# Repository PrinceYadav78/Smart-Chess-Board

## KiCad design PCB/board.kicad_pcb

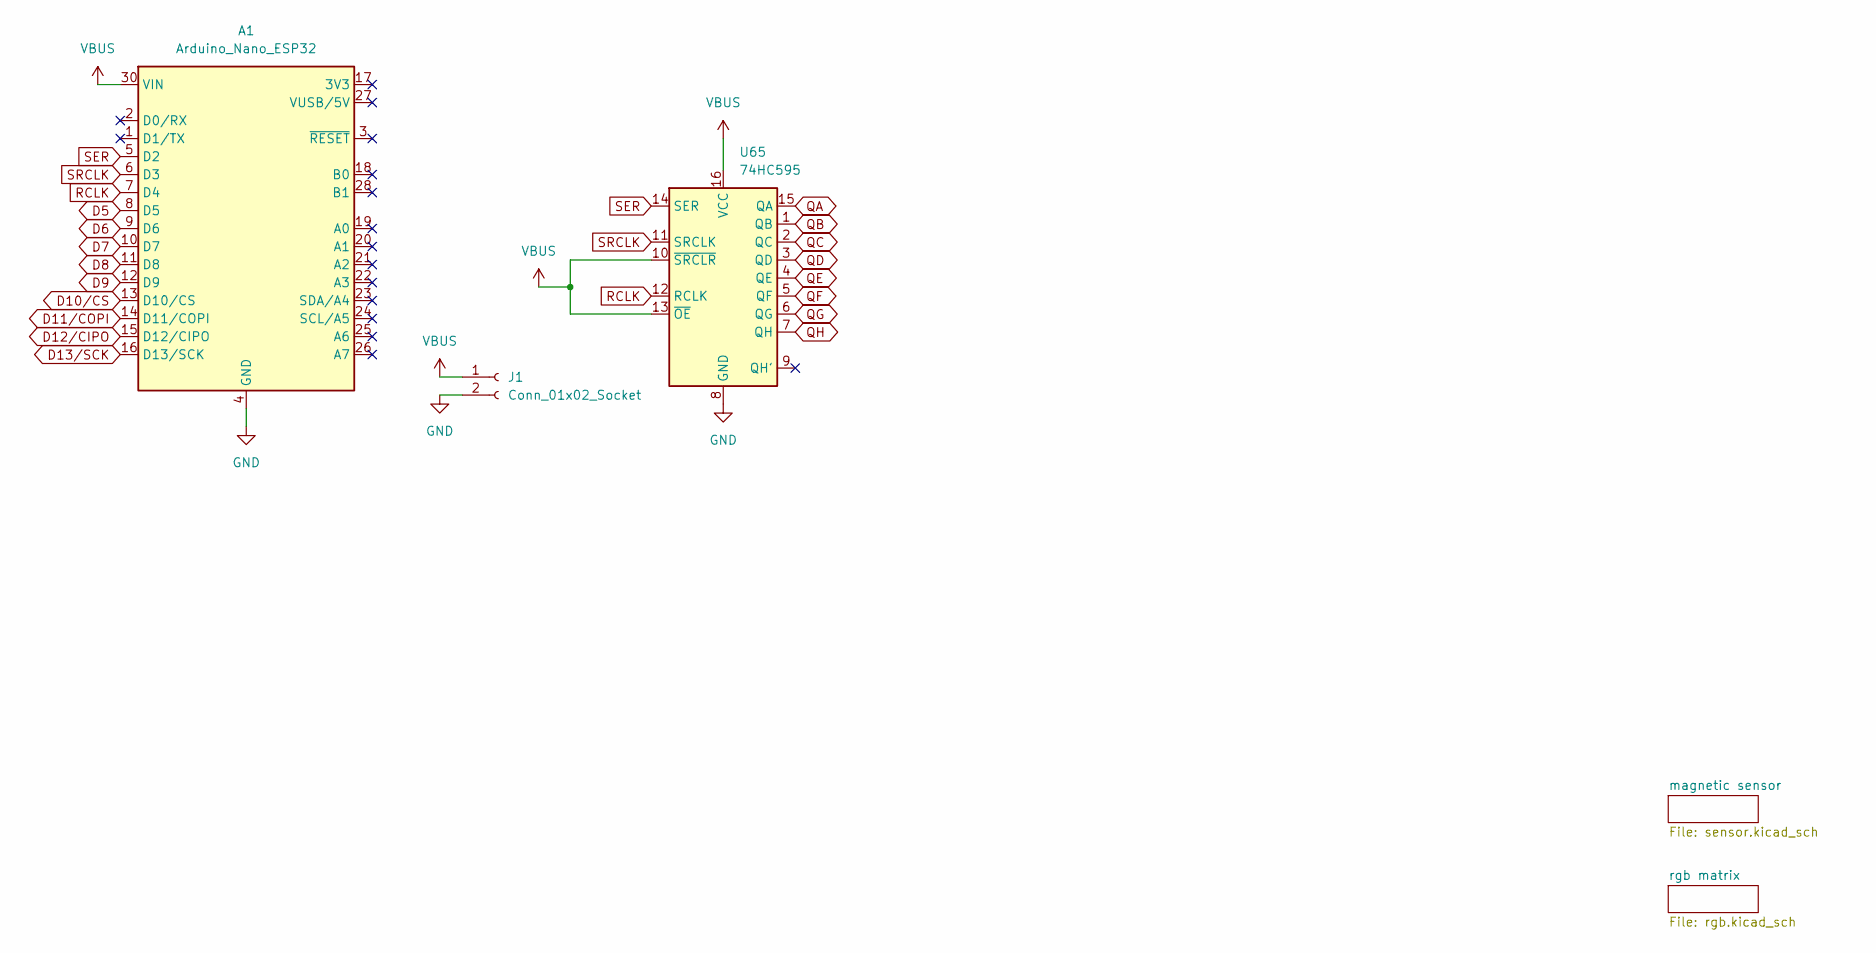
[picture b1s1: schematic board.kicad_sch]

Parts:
A1: Arduino_Nano_ESP32; Arduino_Nano
J1: Conn_01x02_Socket; Hirose_DF63R-2P-3.96DSA_1x02_P3.96mm_Vertical
U65: 74HC595; DIP-16_W7.62mm

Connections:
D5: A1.8 (D5); also elsewhere on the board
D6: A1.9 (D6); also elsewhere on the board
D7: A1.10 (D7); also elsewhere on the board
D8: A1.11 (D8); also elsewhere on the board
D9: A1.12 (D9); also elsewhere on the board
D10/CS: A1.13 (D10/CS); also elsewhere on the board
D11/COPI: A1.14 (D11/COPI); also elsewhere on the board
D12/CIPO: A1.15 (D12/CIPO); also elsewhere on the board
D13/SCK: A1.16 (D13/SCK); also elsewhere on the board
GND: A1.4 (GND), A1.29 (GND), J1.2, U65.8 (GND); also elsewhere on the board
QA: U65.15 (QA); also elsewhere on the board
QB: U65.1 (QB); also elsewhere on the board
QC: U65.2 (QC); also elsewhere on the board
QD: U65.3 (QD); also elsewhere on the board
QE: U65.4 (QE); also elsewhere on the board
QF: U65.5 (QF); also elsewhere on the board
QG: U65.6 (QG); also elsewhere on the board
QH: U65.7 (QH); also elsewhere on the board
RCLK: A1.7 (D4), U65.12 (RCLK)
SER: A1.5 (D2), U65.14 (SER)
SRCLK: A1.6 (D3), U65.11 (SRCLK)
VBUS: A1.30 (VIN), J1.1, U65.10 (~SRCLR), U65.13 (~OE), U65.16 (VCC); also elsewhere on the board

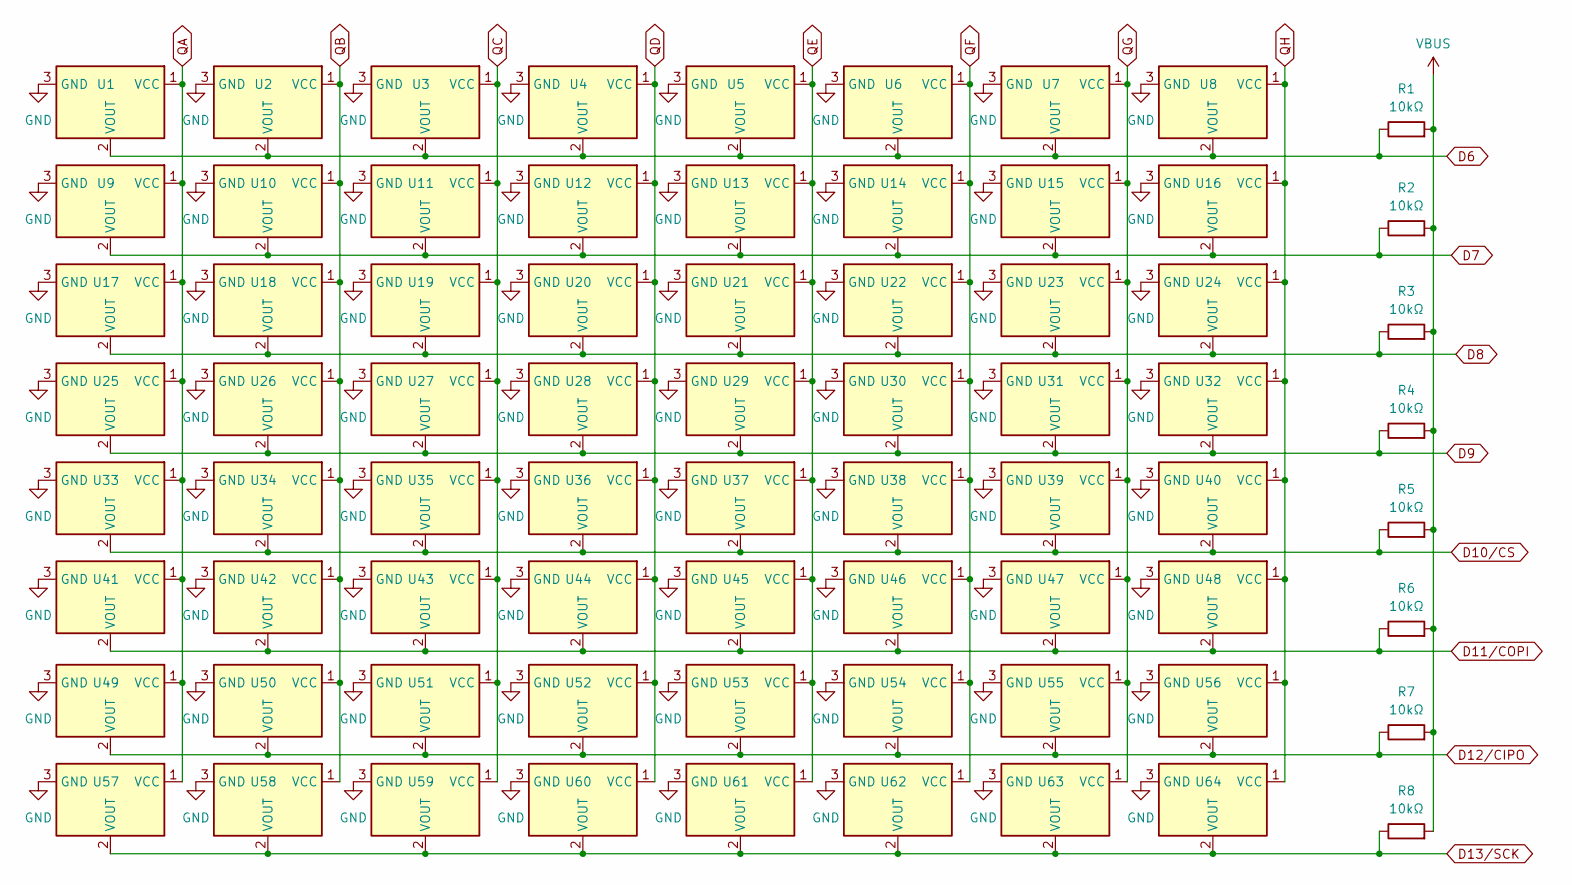
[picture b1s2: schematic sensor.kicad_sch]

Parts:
R1, R2, R3, R4, R5, R6, R7, R8: 10kΩ; R_0805_2012Metric
U1, U2, U3, U4, U5, U6, U7, U8, U9, U10, U11, U12, U13, U14, U15, U16, U17, U18, U19, U20, U21, U22, U23, U24, U25, U26, U27, U28, U29, U30, U31, U32, U33, U34, U35, U36, U37, U38, U39, U40, U41, U42, U43, U44, U45, U46, U47, U48, U49, U50, U51, U52, U53, U54, U55, U56, U57, U58, U59, U60, U61, U62, U63, U64: A3144E; SOT-23

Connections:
D6: R1.1, U1.2 (VOUT), U2.2 (VOUT), U3.2 (VOUT), U4.2 (VOUT), U5.2 (VOUT), U6.2 (VOUT), U7.2 (VOUT), U8.2 (VOUT); also elsewhere on the board
D7: R2.1, U9.2 (VOUT), U10.2 (VOUT), U11.2 (VOUT), U12.2 (VOUT), U13.2 (VOUT), U14.2 (VOUT), U15.2 (VOUT), U16.2 (VOUT); also elsewhere on the board
D8: R3.1, U17.2 (VOUT), U18.2 (VOUT), U19.2 (VOUT), U20.2 (VOUT), U21.2 (VOUT), U22.2 (VOUT), U23.2 (VOUT), U24.2 (VOUT); also elsewhere on the board
D9: R4.1, U25.2 (VOUT), U26.2 (VOUT), U27.2 (VOUT), U28.2 (VOUT), U29.2 (VOUT), U30.2 (VOUT), U31.2 (VOUT), U32.2 (VOUT); also elsewhere on the board
D10/CS: R5.1, U33.2 (VOUT), U34.2 (VOUT), U35.2 (VOUT), U36.2 (VOUT), U37.2 (VOUT), U38.2 (VOUT), U39.2 (VOUT), U40.2 (VOUT); also elsewhere on the board
D11/COPI: R6.1, U41.2 (VOUT), U42.2 (VOUT), U43.2 (VOUT), U44.2 (VOUT), U45.2 (VOUT), U46.2 (VOUT), U47.2 (VOUT), U48.2 (VOUT); also elsewhere on the board
D12/CIPO: R7.1, U49.2 (VOUT), U50.2 (VOUT), U51.2 (VOUT), U52.2 (VOUT), U53.2 (VOUT), U54.2 (VOUT), U55.2 (VOUT), U56.2 (VOUT); also elsewhere on the board
D13/SCK: R8.1, U57.2 (VOUT), U58.2 (VOUT), U59.2 (VOUT), U60.2 (VOUT), U61.2 (VOUT), U62.2 (VOUT), U63.2 (VOUT), U64.2 (VOUT); also elsewhere on the board
GND: U1.3 (GND), U2.3 (GND), U3.3 (GND), U4.3 (GND), U5.3 (GND), U6.3 (GND), U7.3 (GND), U8.3 (GND), U9.3 (GND), U10.3 (GND), U11.3 (GND), U12.3 (GND), U13.3 (GND), U14.3 (GND), U15.3 (GND), U16.3 (GND), U17.3 (GND), U18.3 (GND), U19.3 (GND), U20.3 (GND), U21.3 (GND), U22.3 (GND), U23.3 (GND), U24.3 (GND), U25.3 (GND), U26.3 (GND), U27.3 (GND), U28.3 (GND), U29.3 (GND), U30.3 (GND), U31.3 (GND), U32.3 (GND), U33.3 (GND), U34.3 (GND), U35.3 (GND), U36.3 (GND), U37.3 (GND), U38.3 (GND), U39.3 (GND), U40.3 (GND), U41.3 (GND), U42.3 (GND), U43.3 (GND), U44.3 (GND), U45.3 (GND), U46.3 (GND), U47.3 (GND), U48.3 (GND), U49.3 (GND), U50.3 (GND), U51.3 (GND), U52.3 (GND), U53.3 (GND), U54.3 (GND), U55.3 (GND), U56.3 (GND), U57.3 (GND), U58.3 (GND), U59.3 (GND), U60.3 (GND), U61.3 (GND), U62.3 (GND), U63.3 (GND), U64.3 (GND); also elsewhere on the board
QA: U1.1 (VCC), U9.1 (VCC), U17.1 (VCC), U25.1 (VCC), U33.1 (VCC), U41.1 (VCC), U49.1 (VCC), U57.1 (VCC); also elsewhere on the board
QB: U2.1 (VCC), U10.1 (VCC), U18.1 (VCC), U26.1 (VCC), U34.1 (VCC), U42.1 (VCC), U50.1 (VCC), U58.1 (VCC); also elsewhere on the board
QC: U3.1 (VCC), U11.1 (VCC), U19.1 (VCC), U27.1 (VCC), U35.1 (VCC), U43.1 (VCC), U51.1 (VCC), U59.1 (VCC); also elsewhere on the board
QD: U4.1 (VCC), U12.1 (VCC), U20.1 (VCC), U28.1 (VCC), U36.1 (VCC), U44.1 (VCC), U52.1 (VCC), U60.1 (VCC); also elsewhere on the board
QE: U5.1 (VCC), U13.1 (VCC), U21.1 (VCC), U29.1 (VCC), U37.1 (VCC), U45.1 (VCC), U53.1 (VCC), U61.1 (VCC); also elsewhere on the board
QF: U6.1 (VCC), U14.1 (VCC), U22.1 (VCC), U30.1 (VCC), U38.1 (VCC), U46.1 (VCC), U54.1 (VCC), U62.1 (VCC); also elsewhere on the board
QG: U7.1 (VCC), U15.1 (VCC), U23.1 (VCC), U31.1 (VCC), U39.1 (VCC), U47.1 (VCC), U55.1 (VCC), U63.1 (VCC); also elsewhere on the board
QH: U8.1 (VCC), U16.1 (VCC), U24.1 (VCC), U32.1 (VCC), U40.1 (VCC), U48.1 (VCC), U56.1 (VCC), U64.1 (VCC); also elsewhere on the board
VBUS: R1.2, R2.2, R3.2, R4.2, R5.2, R6.2, R7.2, R8.2; also elsewhere on the board

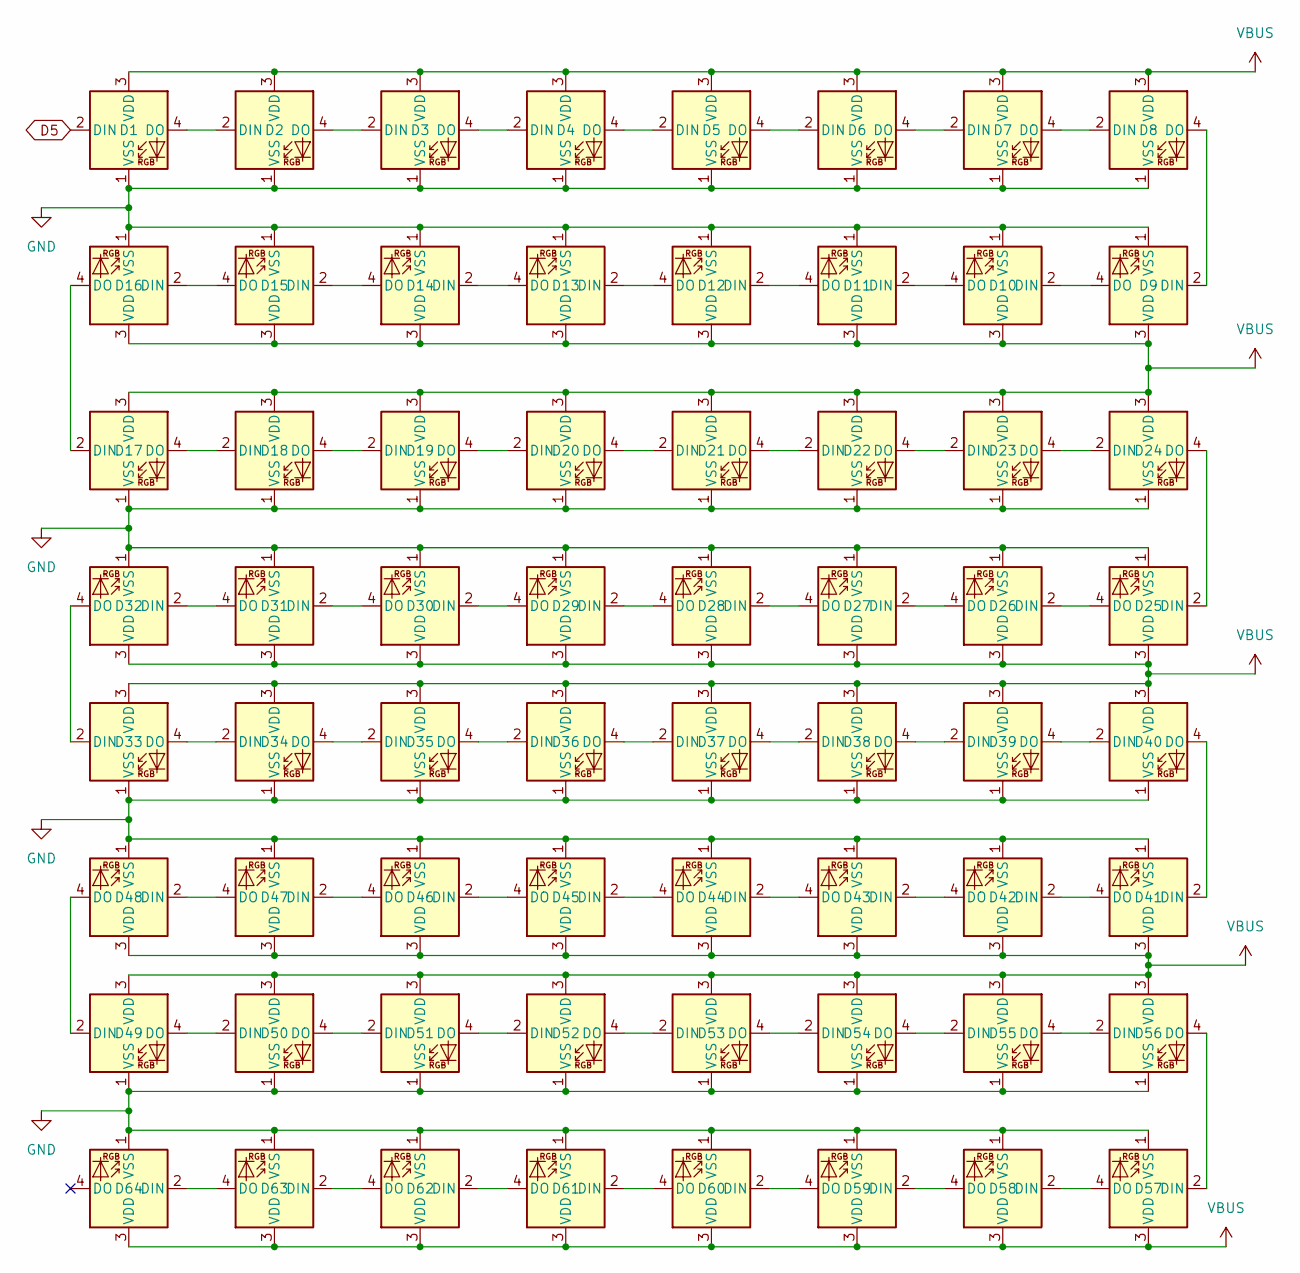
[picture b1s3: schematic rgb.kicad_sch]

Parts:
D1, D2, D3, D4, D5, D6, D7, D8, D9, D10, D11, D12, D13, D14, D15, D16, D17, D18, D19, D20, D21, D22, D23, D24, D25, D26, D27, D28, D29, D30, D31, D32, D33, D34, D35, D36, D37, D38, D39, D40, D41, D42, D43, D44, D45, D46, D47, D48, D49, D50, D51, D52, D53, D54, D55, D56, D57, D58, D59, D60, D61, D62, D63, D64: Inolux_IN-PI554FCH; LED_Inolux_IN-PI554FCH_PLCC4_5.0x5.0mm_P3.2mm

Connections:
D5: D1.2 (DIN); also elsewhere on the board
GND: D1.1 (VSS), D2.1 (VSS), D3.1 (VSS), D4.1 (VSS), D5.1 (VSS), D6.1 (VSS), D7.1 (VSS), D8.1 (VSS), D9.1 (VSS), D10.1 (VSS), D11.1 (VSS), D12.1 (VSS), D13.1 (VSS), D14.1 (VSS), D15.1 (VSS), D16.1 (VSS), D17.1 (VSS), D18.1 (VSS), D19.1 (VSS), D20.1 (VSS), D21.1 (VSS), D22.1 (VSS), D23.1 (VSS), D24.1 (VSS), D25.1 (VSS), D26.1 (VSS), D27.1 (VSS), D28.1 (VSS), D29.1 (VSS), D30.1 (VSS), D31.1 (VSS), D32.1 (VSS), D33.1 (VSS), D34.1 (VSS), D35.1 (VSS), D36.1 (VSS), D37.1 (VSS), D38.1 (VSS), D39.1 (VSS), D40.1 (VSS), D41.1 (VSS), D42.1 (VSS), D43.1 (VSS), D44.1 (VSS), D45.1 (VSS), D46.1 (VSS), D47.1 (VSS), D48.1 (VSS), D49.1 (VSS), D50.1 (VSS), D51.1 (VSS), D52.1 (VSS), D53.1 (VSS), D54.1 (VSS), D55.1 (VSS), D56.1 (VSS), D57.1 (VSS), D58.1 (VSS), D59.1 (VSS), D60.1 (VSS), D61.1 (VSS), D62.1 (VSS), D63.1 (VSS), D64.1 (VSS); also elsewhere on the board
unnamed: D1.4 (DO), D2.2 (DIN)
unnamed: D2.4 (DO), D3.2 (DIN)
unnamed: D3.4 (DO), D4.2 (DIN)
unnamed: D4.4 (DO), D5.2 (DIN)
unnamed: D5.4 (DO), D6.2 (DIN)
unnamed: D6.4 (DO), D7.2 (DIN)
unnamed: D7.4 (DO), D8.2 (DIN)
unnamed: D8.4 (DO), D9.2 (DIN)
unnamed: D9.4 (DO), D10.2 (DIN)
unnamed: D10.4 (DO), D11.2 (DIN)
unnamed: D11.4 (DO), D12.2 (DIN)
unnamed: D12.4 (DO), D13.2 (DIN)
unnamed: D13.4 (DO), D14.2 (DIN)
unnamed: D14.4 (DO), D15.2 (DIN)
unnamed: D15.4 (DO), D16.2 (DIN)
unnamed: D16.4 (DO), D17.2 (DIN)
unnamed: D17.4 (DO), D18.2 (DIN)
unnamed: D18.4 (DO), D19.2 (DIN)
unnamed: D19.4 (DO), D20.2 (DIN)
unnamed: D20.4 (DO), D21.2 (DIN)
unnamed: D21.4 (DO), D22.2 (DIN)
unnamed: D22.4 (DO), D23.2 (DIN)
unnamed: D23.4 (DO), D24.2 (DIN)
unnamed: D24.4 (DO), D25.2 (DIN)
unnamed: D25.4 (DO), D26.2 (DIN)
unnamed: D26.4 (DO), D27.2 (DIN)
unnamed: D27.4 (DO), D28.2 (DIN)
unnamed: D28.4 (DO), D29.2 (DIN)
unnamed: D29.4 (DO), D30.2 (DIN)
unnamed: D30.4 (DO), D31.2 (DIN)
unnamed: D31.4 (DO), D32.2 (DIN)
unnamed: D32.4 (DO), D33.2 (DIN)
unnamed: D33.4 (DO), D34.2 (DIN)
unnamed: D34.4 (DO), D35.2 (DIN)
unnamed: D35.4 (DO), D36.2 (DIN)
unnamed: D36.4 (DO), D37.2 (DIN)
unnamed: D37.4 (DO), D38.2 (DIN)
unnamed: D38.4 (DO), D39.2 (DIN)
unnamed: D39.4 (DO), D40.2 (DIN)
unnamed: D40.4 (DO), D41.2 (DIN)
unnamed: D41.4 (DO), D42.2 (DIN)
unnamed: D42.4 (DO), D43.2 (DIN)
unnamed: D43.4 (DO), D44.2 (DIN)
unnamed: D44.4 (DO), D45.2 (DIN)
unnamed: D45.4 (DO), D46.2 (DIN)
unnamed: D46.4 (DO), D47.2 (DIN)
unnamed: D47.4 (DO), D48.2 (DIN)
unnamed: D48.4 (DO), D49.2 (DIN)
unnamed: D49.4 (DO), D50.2 (DIN)
unnamed: D50.4 (DO), D51.2 (DIN)
unnamed: D51.4 (DO), D52.2 (DIN)
unnamed: D52.4 (DO), D53.2 (DIN)
unnamed: D53.4 (DO), D54.2 (DIN)
unnamed: D54.4 (DO), D55.2 (DIN)
unnamed: D55.4 (DO), D56.2 (DIN)
unnamed: D56.4 (DO), D57.2 (DIN)
unnamed: D57.4 (DO), D58.2 (DIN)
unnamed: D58.4 (DO), D59.2 (DIN)
unnamed: D59.4 (DO), D60.2 (DIN)
unnamed: D60.4 (DO), D61.2 (DIN)
unnamed: D61.4 (DO), D62.2 (DIN)
unnamed: D62.4 (DO), D63.2 (DIN)
unnamed: D63.4 (DO), D64.2 (DIN)
VBUS: D1.3 (VDD), D2.3 (VDD), D3.3 (VDD), D4.3 (VDD), D5.3 (VDD), D6.3 (VDD), D7.3 (VDD), D8.3 (VDD), D9.3 (VDD), D10.3 (VDD), D11.3 (VDD), D12.3 (VDD), D13.3 (VDD), D14.3 (VDD), D15.3 (VDD), D16.3 (VDD), D17.3 (VDD), D18.3 (VDD), D19.3 (VDD), D20.3 (VDD), D21.3 (VDD), D22.3 (VDD), D23.3 (VDD), D24.3 (VDD), D25.3 (VDD), D26.3 (VDD), D27.3 (VDD), D28.3 (VDD), D29.3 (VDD), D30.3 (VDD), D31.3 (VDD), D32.3 (VDD), D33.3 (VDD), D34.3 (VDD), D35.3 (VDD), D36.3 (VDD), D37.3 (VDD), D38.3 (VDD), D39.3 (VDD), D40.3 (VDD), D41.3 (VDD), D42.3 (VDD), D43.3 (VDD), D44.3 (VDD), D45.3 (VDD), D46.3 (VDD), D47.3 (VDD), D48.3 (VDD), D49.3 (VDD), D50.3 (VDD), D51.3 (VDD), D52.3 (VDD), D53.3 (VDD), D54.3 (VDD), D55.3 (VDD), D56.3 (VDD), D57.3 (VDD), D58.3 (VDD), D59.3 (VDD), D60.3 (VDD), D61.3 (VDD), D62.3 (VDD), D63.3 (VDD), D64.3 (VDD); also elsewhere on the board

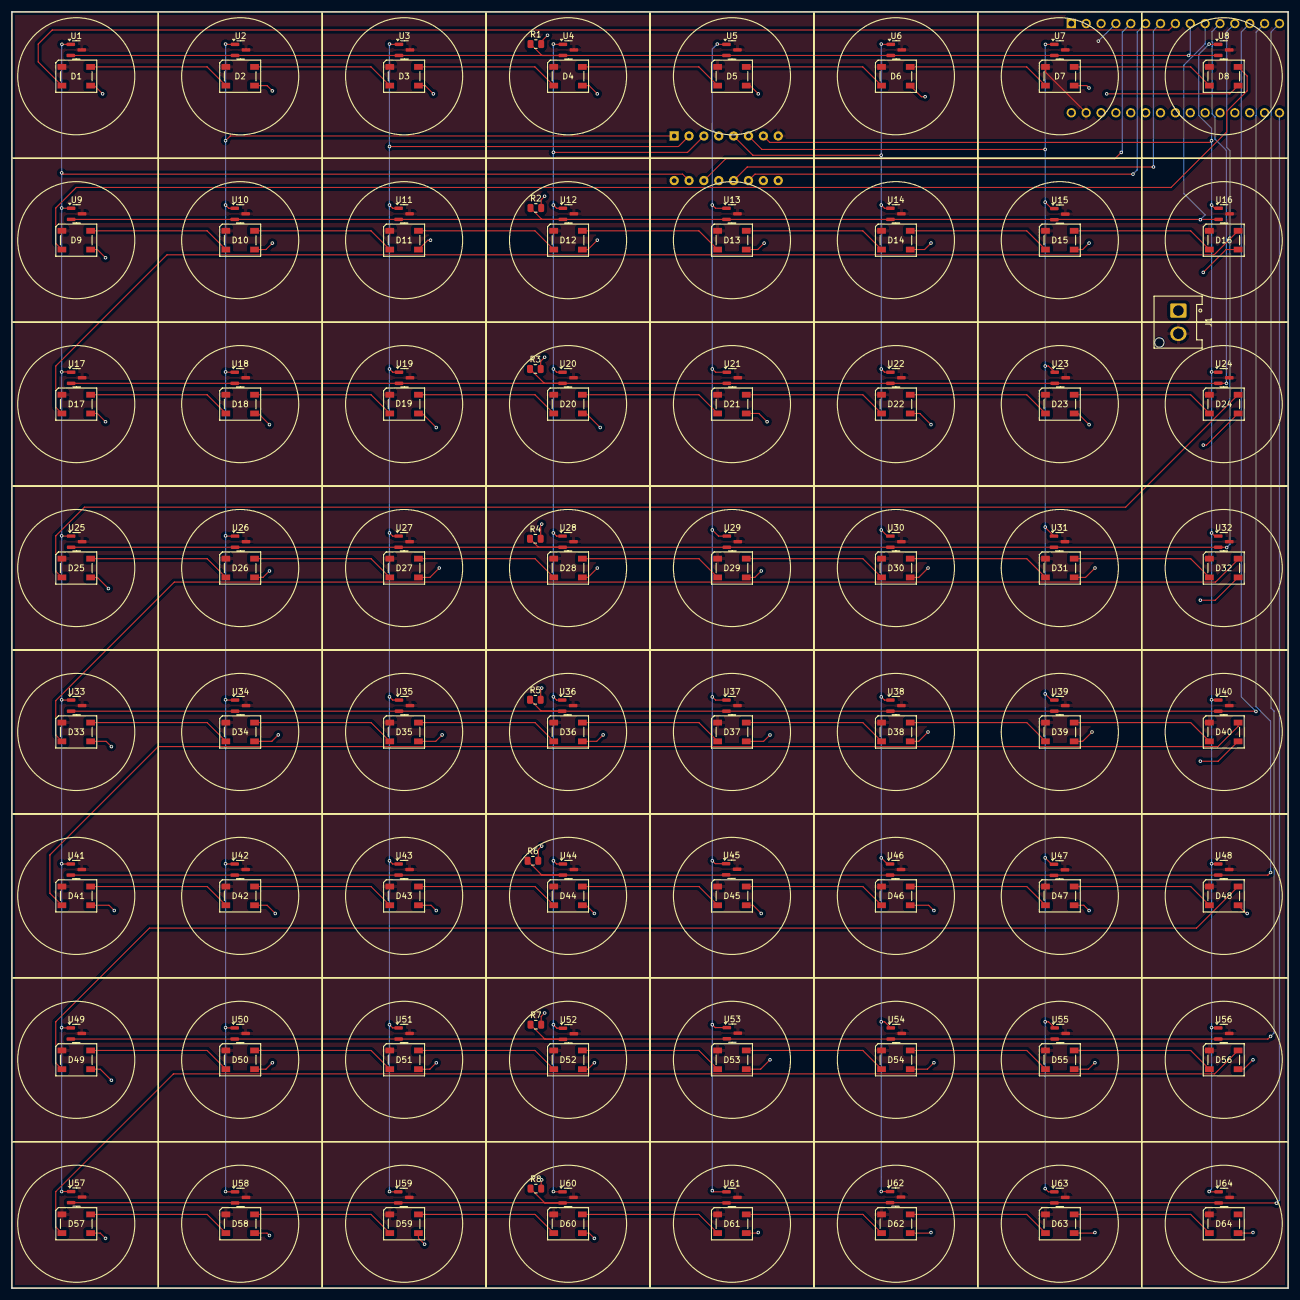
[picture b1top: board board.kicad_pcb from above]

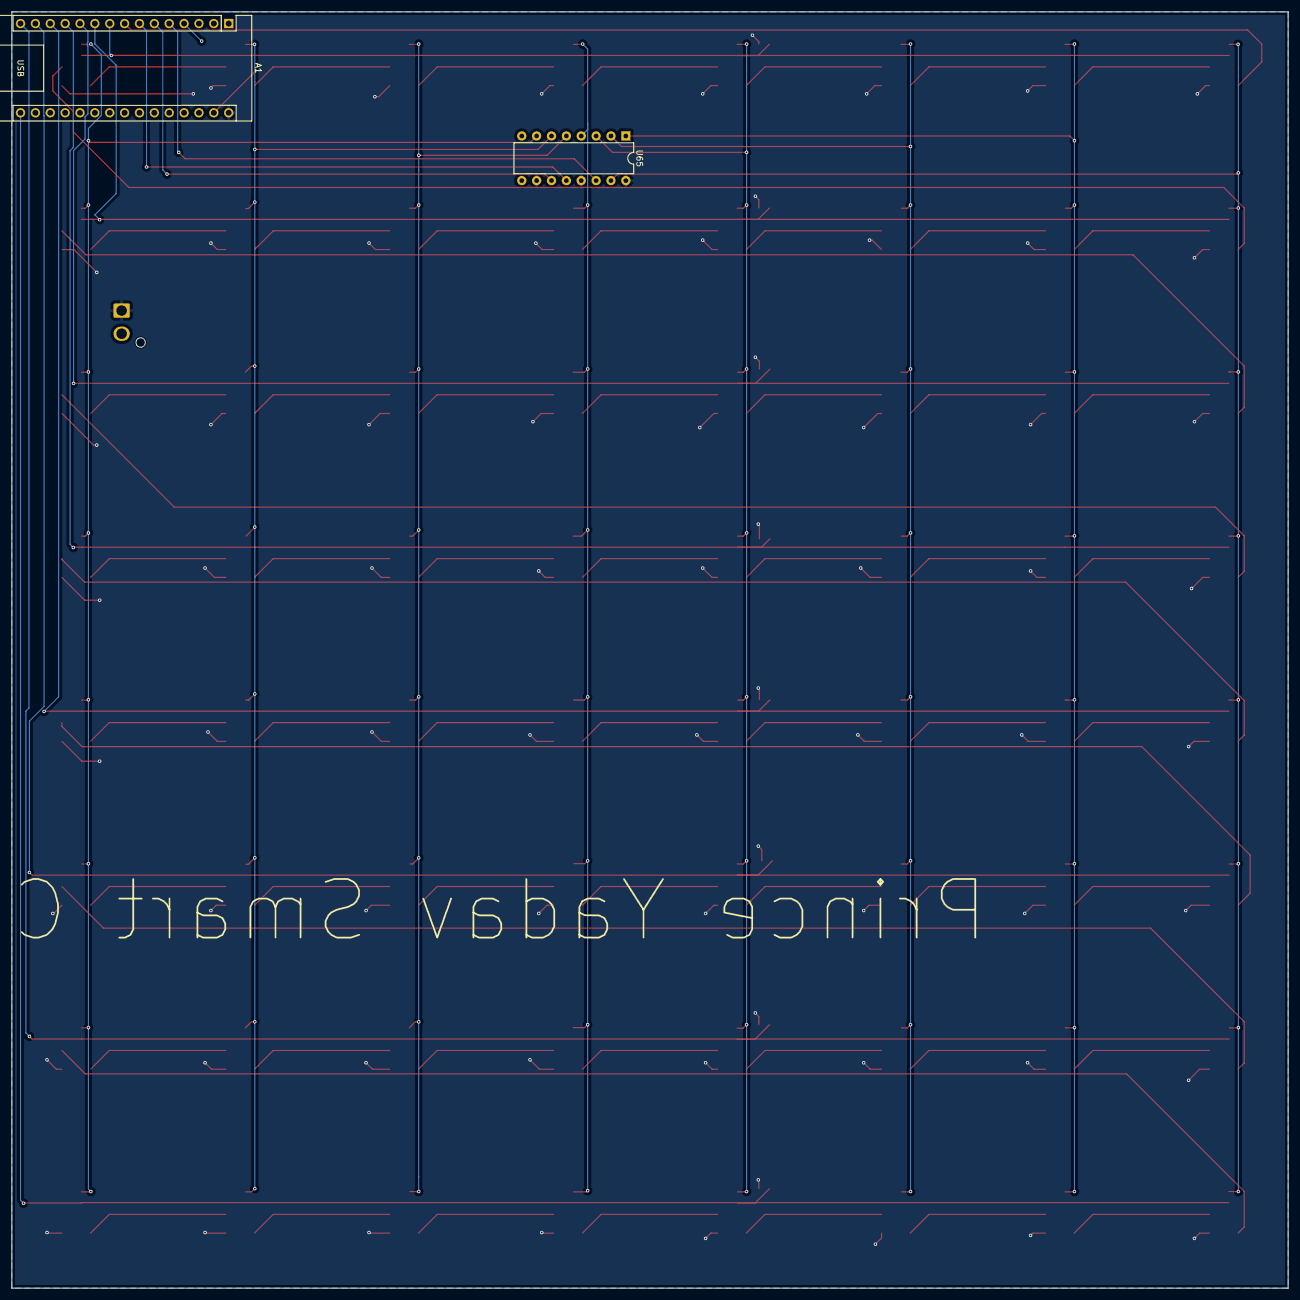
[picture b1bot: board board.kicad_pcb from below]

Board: 2 copper layers, 218.0 x 218.0 mm, 139 parts (2 on the bottom side), 85 nets.

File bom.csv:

Designator,Footprint,Quantity,Value,LCSC Part #
A1,Arduino_Nano,1,Arduino_Nano_ESP32,
"D1, D10, D11, D12, D13, D14, D15, D16, D17, D18, D19, D2, D20, D21, D22, D23, D24, D25, D26, D27, D28, D29, D3, D30, D31, D32, D33, D34, D35, D36, D37, D38, D39, D4, D40, D41, D42, D43, D44, D45, D46, D47, D48, D49, D5, D50, D51, D52, D53, D54, D55, D56, D57, D58, D59, D6, D60, D61, D62, D63, D64, D7, D8, D9",LED_Inolux_IN-PI554FCH_PLCC4_5.0x5.0mm_P3.2mm,64,Inolux_IN-PI554FCH,
J1,Hirose_DF63R-2P-3.96DSA_1x02_P3.96mm_Vertical,1,Conn_01x02_Socket,
"R1, R2, R3, R4, R5, R6, R7, R8",0805,8,10kΩ,
"U1, U10, U11, U12, U13, U14, U15, U16, U17, U18, U19, U2, U20, U21, U22, U23, U24, U25, U26, U27, U28, U29, U3, U30, U31, U32, U33, U34, U35, U36, U37, U38, U39, U4, U40, U41, U42, U43, U44, U45, U46, U47, U48, U49, U5, U50, U51, U52, U53, U54, U55, U56, U57, U58, U59, U6, U60, U61, U62, U63, U64, U7, U8, U9",SOT-23,64,A3144E,
U65,DIP-16_W7.62mm,1,74HC595,

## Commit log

2026-01-07 added Step Cad files folder
2026-01-07 adding all chess project files
2026-01-07 Add images to README.md
    Added multiple images to the README file.
